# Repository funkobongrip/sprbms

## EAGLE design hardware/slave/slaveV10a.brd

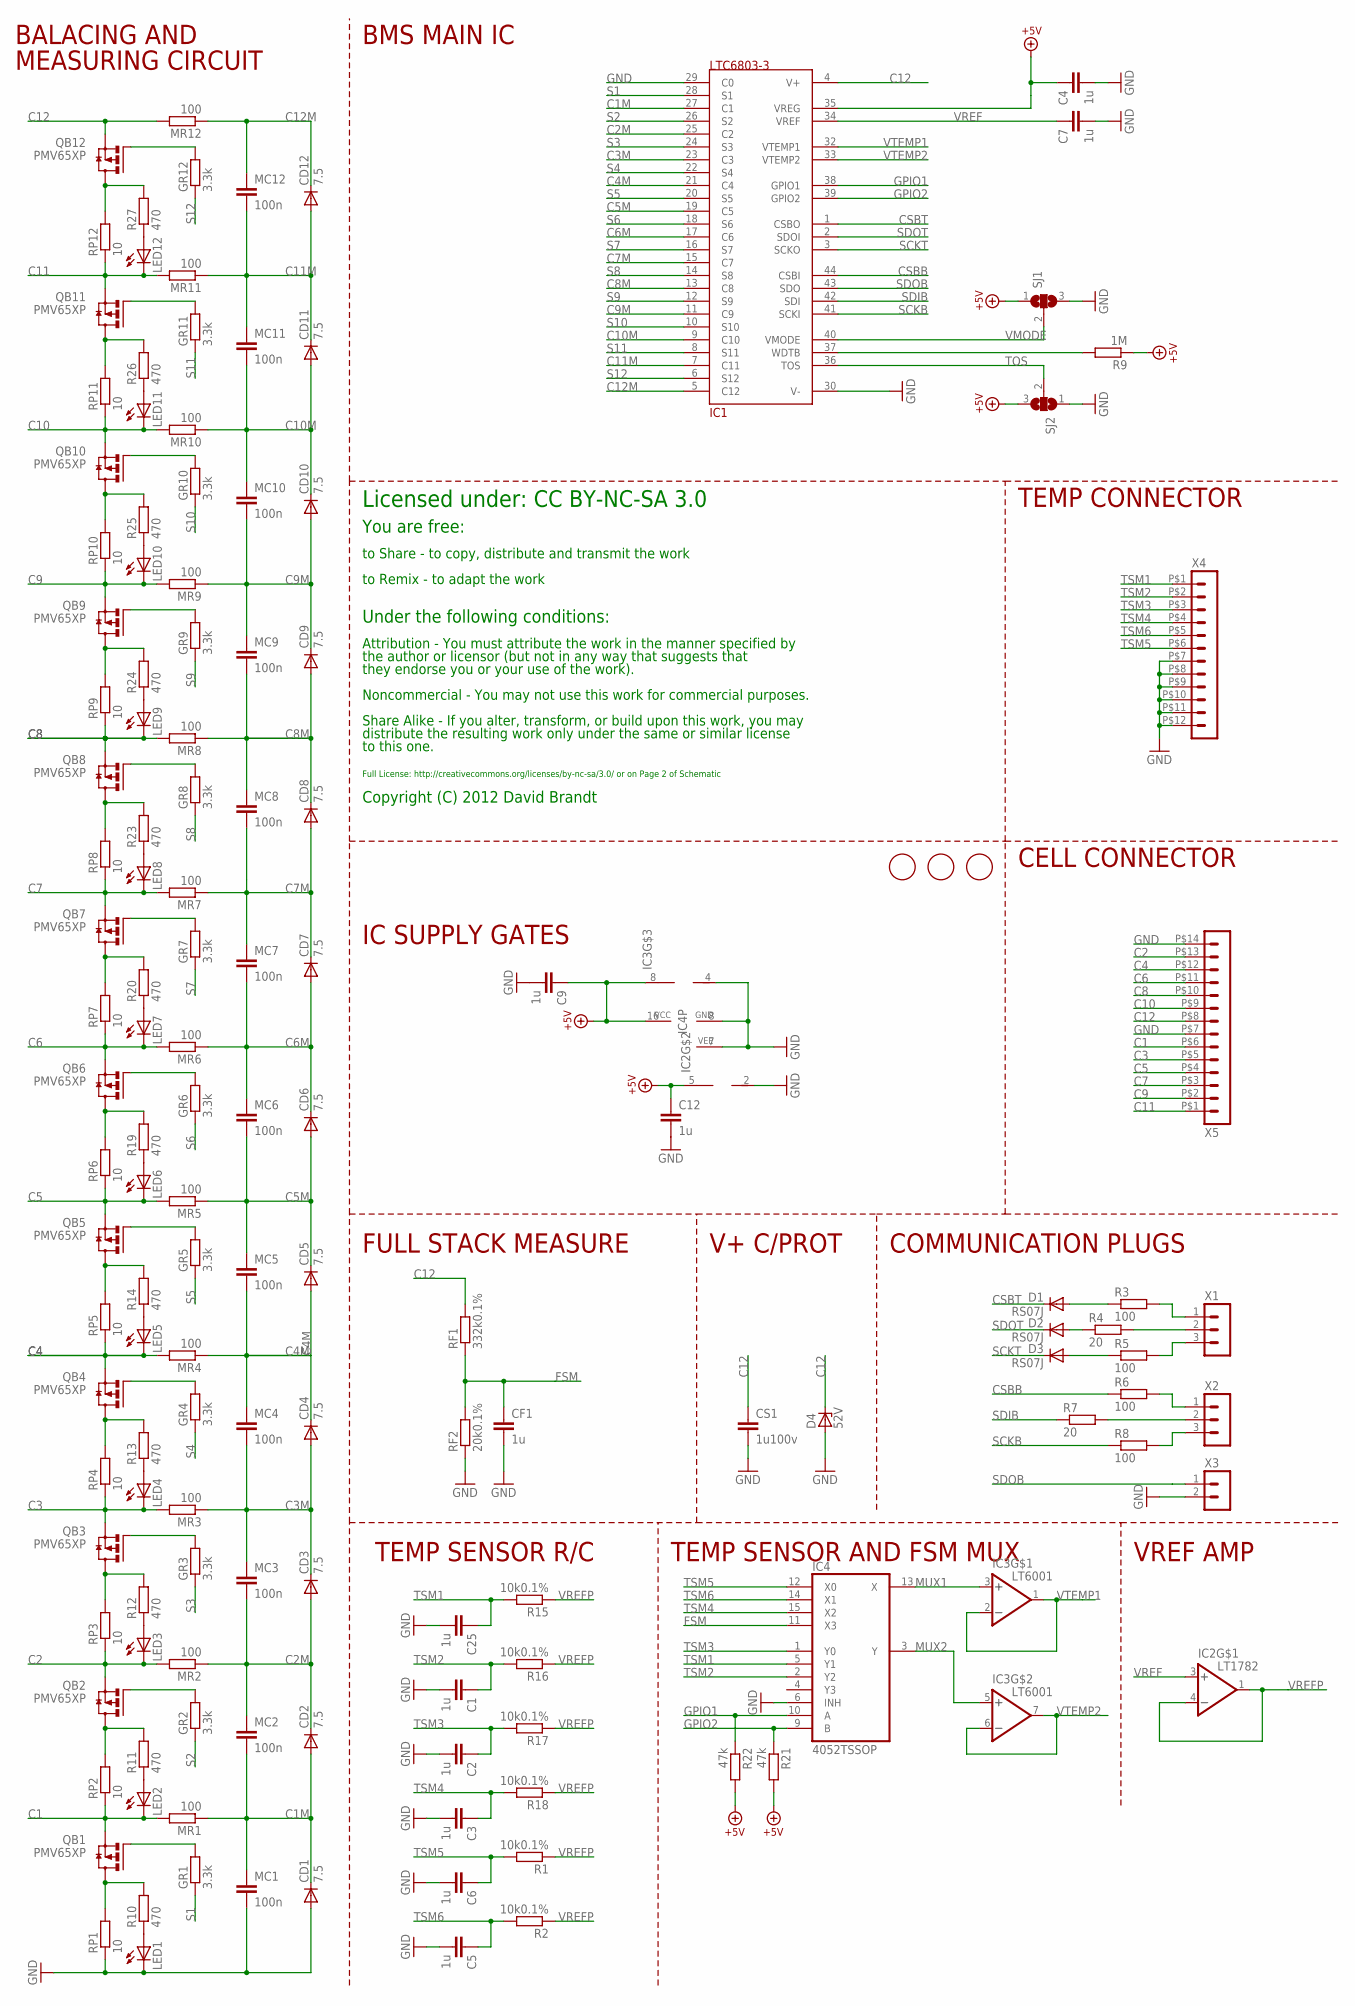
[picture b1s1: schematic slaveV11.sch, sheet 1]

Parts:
C1, C2, C3, C4, C5, C6, C7, C9, C12, C25: 1u; C0603
CD1, CD2, CD3, CD4, CD5, CD6, CD7, CD8, CD9, CD10, CD11, CD12: 7.5; SOD323-W
CF1: 1u; C0603
CS1: 1u100v; C1206K
D1, D2, D3: RS07J; DO-219AB
D4: 52V; SOD123
GR1, GR2, GR3, GR4, GR5, GR6, GR7, GR8, GR9, GR10, GR11, GR12: 3.3k; R0603
IC1: LTC6803-3; 44SSOP
IC2: LT1782; SOT23-5
IC3: LT6001; MS8
IC4: 4052TSSOP; TSSOP16
LED1, LED2, LED3, LED4, LED5, LED6, LED7, LED8, LED9, LED10, LED11, LED12: LEDCHIPLED_0805; CHIPLED_0805
MC1, MC2, MC3, MC4, MC5, MC6, MC7, MC8, MC9, MC10, MC11, MC12: 100n; C1206
MR1, MR2, MR3, MR4, MR5, MR6, MR7, MR8, MR9, MR10, MR11, MR12: 100; R0603
QB1, QB2, QB3, QB4, QB5, QB6, QB7, QB8, QB9, QB10, QB11, QB12: PMV65XP; SUPER-SOT3
R1, R2, R15, R16, R17, R18: 10k0.1%; R0603
R3, R5, R6, R8: 100; R0805
R4, R7: 20; R0805
R9: 1M; R0603
R10, R11, R12, R13, R14, R19, R20, R23, R24, R25, R26, R27: 470; R0603
R21, R22: 47k; R0603
REF1, REF2, REF3: FIDUCIALMOUNT; FIDUCIA-MOUNT
RF1: 332k0.1%; R0603
RF2: 20k0.1%; R0603
RP1, RP2, RP3, RP4, RP5, RP6, RP7, RP8, RP9, RP10, RP11, RP12: 10; SM_3
SJ1, SJ2: SJ2W; SJ_2
X1, X2: HEADER_POS3_43650-0315; 43650-0315
X3: HEADER_POS2_43650-0215; 43650-0215
X4: HEADER_POS12_43045-1212; 43045-1212
X5: HEADER_POS14_43045-1412; 43045-1412

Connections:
+5V: C4.1, C9.1, C12.1, IC1.35 (VREG), IC2.5 (V+), IC3.8 (V+), IC4.16 (VCC), R9.1, R21.2, R22.2, SJ1.1, SJ2.3
B1: QB1.3 (D), R10.2, RP1.P$2 (2)
B2: QB2.3 (D), R11.2, RP2.P$2 (2)
B3: QB3.3 (D), R12.2, RP3.P$2 (2)
B4: QB4.3 (D), R13.2, RP4.P$2 (2)
B5: QB5.3 (D), R14.2, RP5.P$2 (2)
B6: QB6.3 (D), R19.2, RP6.P$2 (2)
B7: QB7.3 (D), R20.2, RP7.P$2 (2)
B8: QB8.3 (D), R23.2, RP8.P$2 (2)
B9: QB9.3 (D), R24.2, RP9.P$2 (2)
B10: QB10.3 (D), R25.2, RP10.P$2 (2)
B11: QB11.3 (D), R26.2, RP11.P$2 (2)
B12: QB12.3 (D), R27.2, RP12.P$2 (2)
C1: LED2.C, MR1.2, QB1.2 (S), RP2.P$1 (1), X5.P$6 (6)
C1M: CD1.C, CD2.A, IC1.27 (C1), MC1.1, MC2.2, MR1.1
C2: LED3.C, MR2.2, QB2.2 (S), RP3.P$1 (1), X5.P$13 (13)
C2M: CD2.C, CD3.A, IC1.25 (C2), MC2.1, MC3.2, MR2.1
C3: LED4.C, MR3.2, QB3.2 (S), RP4.P$1 (1), X5.P$5 (5)
C3M: CD3.C, CD4.A, IC1.23 (C3), MC3.1, MC4.2, MR3.1
C4: LED5.C, MR4.2, QB4.2 (S), RP5.P$1 (1), X5.P$12 (12)
C4M: CD4.C, CD5.A, IC1.21 (C4), MC4.1, MC5.2, MR4.1
C5: LED6.C, MR5.2, QB5.2 (S), RP6.P$1 (1), X5.P$4 (4)
C5M: CD5.C, CD6.A, IC1.19 (C5), MC5.1, MC6.2, MR5.1
C6: LED7.C, MR6.2, QB6.2 (S), RP7.P$1 (1), X5.P$11 (11)
C6M: CD6.C, CD7.A, IC1.17 (C6), MC6.1, MC7.2, MR6.1
C7: LED8.C, MR7.2, QB7.2 (S), RP8.P$1 (1), X5.P$3 (3)
C7M: CD7.C, CD8.A, IC1.15 (C7), MC7.1, MC8.2, MR7.1
C8: LED9.C, MR8.2, QB8.2 (S), RP9.P$1 (1), X5.P$10 (10)
C8M: CD8.C, CD9.A, IC1.13 (C8), MC8.1, MC9.2, MR8.1
C9: LED10.C, MR9.2, QB9.2 (S), RP10.P$1 (1), X5.P$2 (2)
C9M: CD9.C, CD10.A, IC1.11 (C9), MC9.1, MC10.2, MR9.1
C10: LED11.C, MR10.2, QB10.2 (S), RP11.P$1 (1), X5.P$9 (9)
C10M: CD10.C, CD11.A, IC1.9 (C10), MC10.1, MC11.2, MR10.1
C11: LED12.C, MR11.2, QB11.2 (S), RP12.P$1 (1), X5.P$1 (1)
C11M: CD11.C, CD12.A, IC1.7 (C11), MC11.1, MC12.2, MR11.1
C12: CS1.1, D4.C, IC1.4 (V+), MR12.2, QB12.2 (S), RF1.2, X5.P$8 (8)
C12M: CD12.C, IC1.5 (C12), MC12.1, MR12.1
CSBB: IC1.44 (CSBI), R6.1
CSBBP: R6.2, X2.1
CSBT: D1.C, IC1.1 (CSBO)
CSBTK: D1.A, R3.1
CSBTP: R3.2, X1.1
FSM: CF1.1, IC4.11 (X3), RF1.1, RF2.2
GND: C1.2, C2.2, C3.2, C4.2, C5.2, C6.2, C7.2, C9.2, C12.2, C25.2, CD1.A, CF1.2, CS1.2, D4.A, IC1.29 (C0), IC1.30 (V-), IC2.2 (V-), IC3.4 (V-), IC4.6 (INH), IC4.7 (VEE), IC4.8 (GND), LED1.C, MC1.2, RF2.1, RP1.P$1 (1), SJ1.3, SJ2.1, X3.2, X4.P$7 (7), X4.P$8 (8), X4.P$9 (9), X4.P$10 (10), X4.P$11 (11), X4.P$12 (12), X5.P$7 (7), X5.P$14 (14)
GPIO1: IC1.38 (GPIO1), IC4.10 (A), R22.1
GPIO2: IC1.39 (GPIO2), IC4.9 (B), R21.1
L1C: LED1.A, R10.1
L2C: LED2.A, R11.1
L3C: LED3.A, R12.1
L4C: LED4.A, R13.1
L5C: LED5.A, R14.1
L6C: LED6.A, R19.1
L7C: LED7.A, R20.1
L8C: LED8.A, R23.1
L9C: LED9.A, R24.1
L10C: LED10.A, R25.1
L11C: LED11.A, R26.1
L12C: LED12.A, R27.1
MUX1: IC3.3 (+IN), IC4.13 (X)
MUX2: IC3.5 (+IN), IC4.3 (Y)
S1: GR1.1, IC1.28 (S1)
S1G: GR1.2, QB1.1 (G)
S1G1: GR2.2, QB2.1 (G)
S1G2: GR3.2, QB3.1 (G)
S1G3: GR4.2, QB4.1 (G)
S1G4: GR5.2, QB5.1 (G)
S1G5: GR6.2, QB6.1 (G)
S1G6: GR7.2, QB7.1 (G)
S1G7: GR8.2, QB8.1 (G)
S1G8: GR9.2, QB9.1 (G)
S1G9: GR10.2, QB10.1 (G)
S1G10: GR11.2, QB11.1 (G)
S1G11: GR12.2, QB12.1 (G)
S2: GR2.1, IC1.26 (S2)
S3: GR3.1, IC1.24 (S3)
S4: GR4.1, IC1.22 (S4)
S5: GR5.1, IC1.20 (S5)
S6: GR6.1, IC1.18 (S6)
S7: GR7.1, IC1.16 (S7)
S8: GR8.1, IC1.14 (S8)
S9: GR9.1, IC1.12 (S9)
S10: GR10.1, IC1.10 (S10)
S11: GR11.1, IC1.8 (S11)
S12: GR12.1, IC1.6 (S12)
SCKB: IC1.41 (SCKI), R8.1
SCKBP: R8.2, X2.3
SCKT: D3.C, IC1.3 (SCKO)
SCKTK: D3.A, R5.1
SCKTP: R5.2, X1.3
SDIB: IC1.42 (SDI), R7.1
SDIBP: R7.2, X2.2
SDOB: IC1.43 (SDO), X3.1
SDOT: D2.C, IC1.2 (SDOI)
SDOTK: D2.A, R4.1
SDOTP: R4.2, X1.2
TOS: IC1.36 (TOS), SJ2.2
TSM1: C25.1, IC4.5 (Y1), R15.2, X4.P$1 (1)
TSM2: C1.1, IC4.2 (Y2), R16.2, X4.P$2 (2)
TSM3: C2.1, IC4.1 (Y0), R17.2, X4.P$3 (3)
TSM4: C3.1, IC4.15 (X2), R18.2, X4.P$4 (4)
TSM5: C6.1, IC4.12 (X0), R1.2, X4.P$6 (6)
TSM6: C5.1, IC4.14 (X1), R2.2, X4.P$5 (5)
VMODE: IC1.40 (VMODE), SJ1.2
VREF: C7.1, IC1.34 (VREF), IC2.3 (+IN)
VREFP: IC2.1 (OUT), IC2.4 (-IN), R1.1, R2.1, R15.1, R16.1, R17.1, R18.1
VTEMP1: IC1.32 (VTEMP1), IC3.1 (OUT), IC3.2 (-IN)
VTEMP2: IC1.33 (VTEMP2), IC3.6 (-IN), IC3.7 (OUT)
WDTB: IC1.37 (WDTB), R9.2

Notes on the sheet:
TEMP CONNECTOR
CELL CONNECTOR
IC SUPPLY GATES
BALACING AND
BMS MAIN IC
TEMP SENSOR AND FSM MUX
MEASURING CIRCUIT
TEMP SENSOR R/C
VREF AMP
FULL STACK MEASURE
V+ C/PROT
COMMUNICATION PLUGS
Licensed under: CC BY-NC-SA 3.0
You are free:
to Share - to copy, distribute and transmit the work
to Remix - to adapt the work
Under the following conditions:
the author or licensor (but not in any way that suggests that
Attribution - You must attribute the work in the manner specified by
they endorse you or your use of the work).
Noncommercial - You may not use this work for commercial purposes.
Share Alike - If you alter, transform, or build upon this work, you may
distribute the resulting work only under the same or similar license
to this one.
Full License: http://creativecommons.org/licenses/by-nc-sa/3.0/ or on Page 2 of Schematic
Copyright (C) 2012 David Brandt

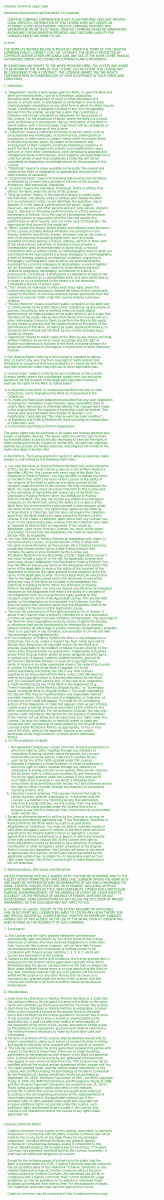
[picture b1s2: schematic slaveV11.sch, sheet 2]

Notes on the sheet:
Creative Commons Legal Code
Attribution-NonCommercial-ShareAlike 3.0 Unported
CREATIVE COMMONS CORPORATION IS NOT A LAW FIRM AND DOES NOT PROVIDE
LEGAL SERVICES. DISTRIBUTION OF THIS LICENSE DOES NOT CREATE AN
ATTORNEY-CLIENT RELATIONSHIP. CREATIVE COMMONS PROVIDES THIS
INFORMATION ON AN "AS-IS" BASIS. CREATIVE COMMONS MAKES NO WARRANTIES
REGARDING THE INFORMATION PROVIDED, AND DISCLAIMS LIABILITY FOR
DAMAGES RESULTING FROM ITS USE.
License
THE WORK (AS DEFINED BELOW) IS PROVIDED UNDER THE TERMS OF THIS CREATIVE
COMMONS PUBLIC LICENSE ("CCPL" OR "LICENSE"). THE WORK IS PROTECTED BY
COPYRIGHT AND/OR OTHER APPLICABLE LAW. ANY USE OF THE WORK OTHER THAN AS
AUTHORIZED UNDER THIS LICENSE OR COPYRIGHT LAW IS PROHIBITED.
BY EXERCISING ANY RIGHTS TO THE WORK PROVIDED HERE, YOU ACCEPT AND AGREE
TO BE BOUND BY THE TERMS OF THIS LICENSE. TO THE EXTENT THIS LICENSE MAY
BE CONSIDERED TO BE A CONTRACT, THE LICENSOR GRANTS YOU THE RIGHTS
CONTAINED HERE IN CONSIDERATION OF YOUR ACCEPTANCE OF SUCH TERMS AND
CONDITIONS.
1. Definitions
a. "Adaptation" means a work based upon the Work, or upon the Work and
other pre-existing works, such as a translation, adaptation,
derivative work, arrangement of music or other alterations of a
literary or artistic work, or phonogram or performance and includes
cinematographic adaptations or any other form in which the Work may be
recast, transformed, or adapted including in any form recognizably
derived from the original, except that a work that constitutes a
Collection will not be considered an Adaptation for the purpose of
this License. For the avoidance of doubt, where the Work is a musical
work, performance or phonogram, the synchronization of the Work in
timed-relation with a moving image ("synching") will be considered an
Adaptation for the purpose of this License.
b. "Collection" means a collection of literary or artistic works, such as
encyclopedias and anthologies, or performances, phonograms or
broadcasts, or other works or subject matter other than works listed
in Section 1(g) below, which, by reason of the selection and
arrangement of their contents, constitute intellectual creations, in
which the Work is included in its entirety in unmodified form along
with one or more other contributions, each constituting separate and
independent works in themselves, which together are assembled into a
collective whole. A work that constitutes a Collection will not be

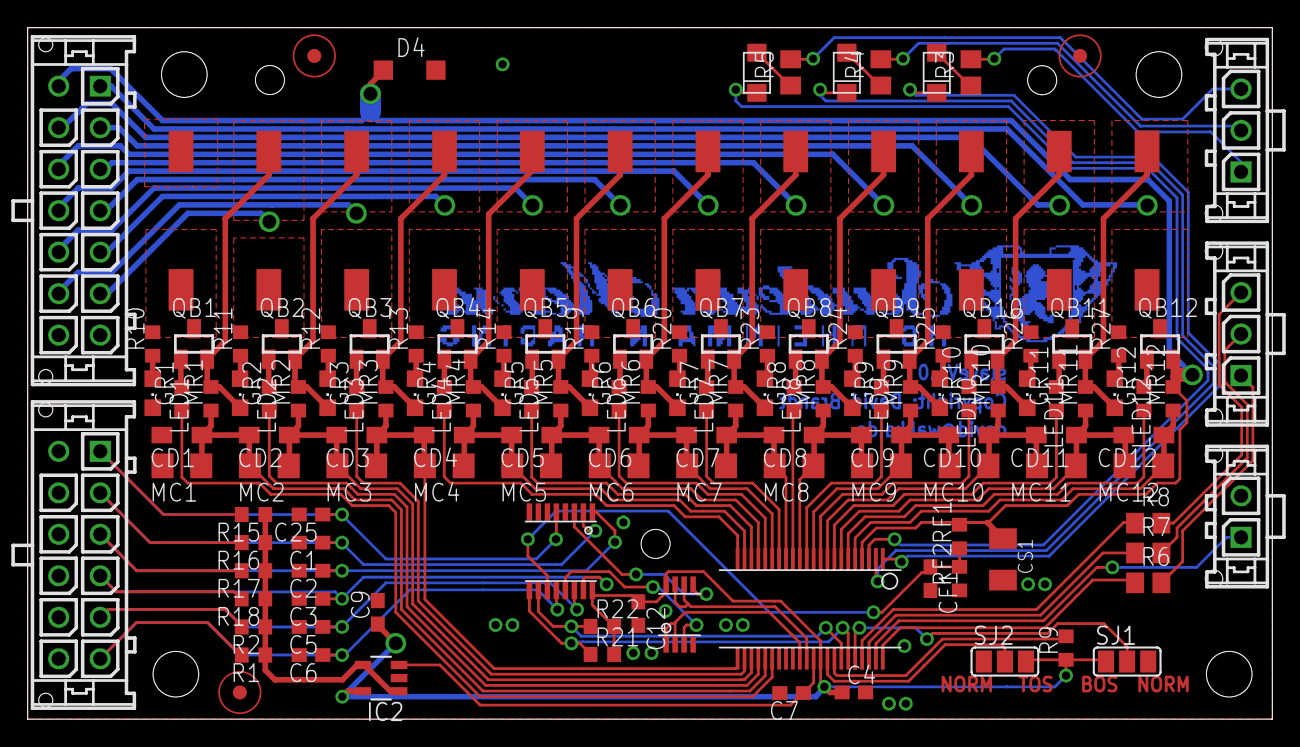
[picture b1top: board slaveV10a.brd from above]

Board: 2 copper layers, 90.0 x 50.0 mm, 144 parts (1 on the bottom side), 108 nets.

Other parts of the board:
U$7: SMLOGO

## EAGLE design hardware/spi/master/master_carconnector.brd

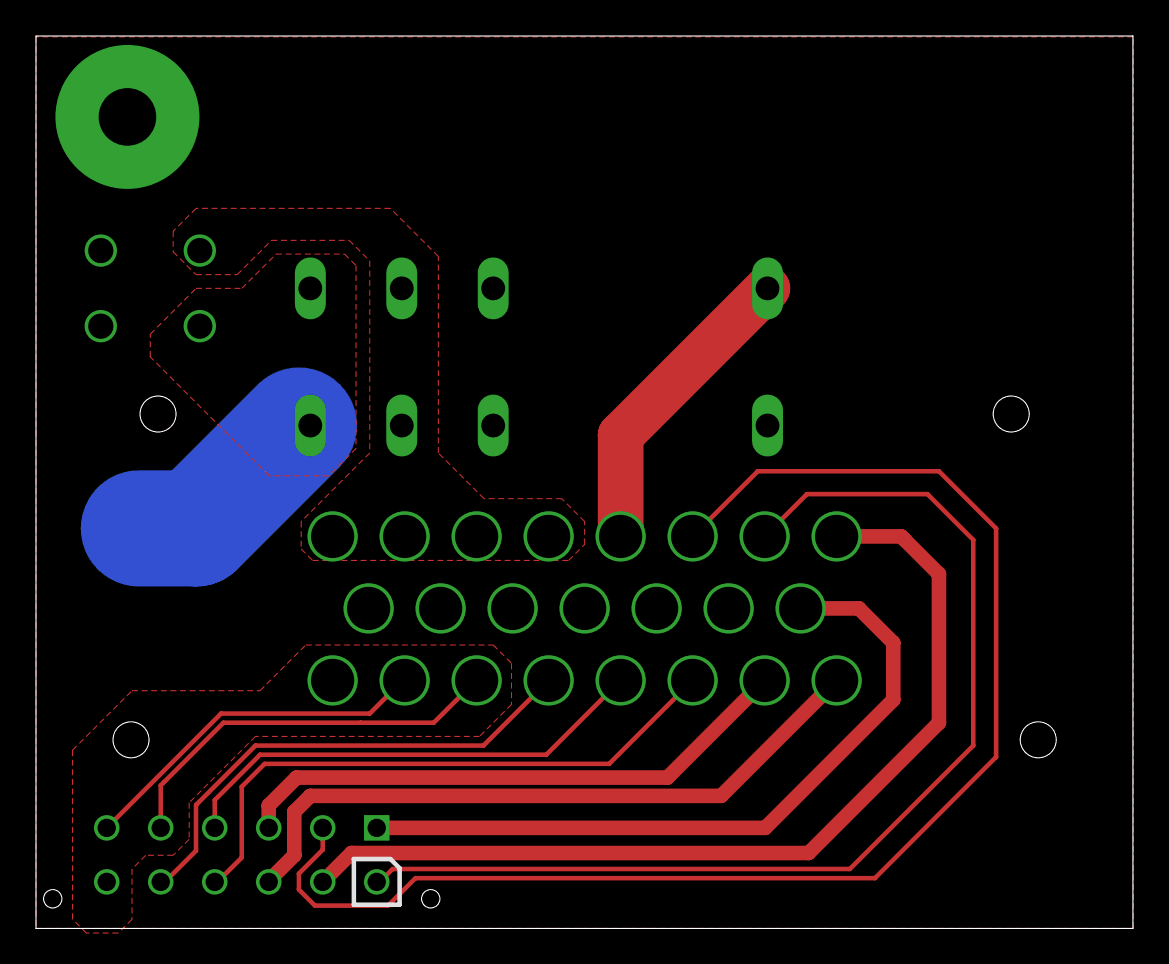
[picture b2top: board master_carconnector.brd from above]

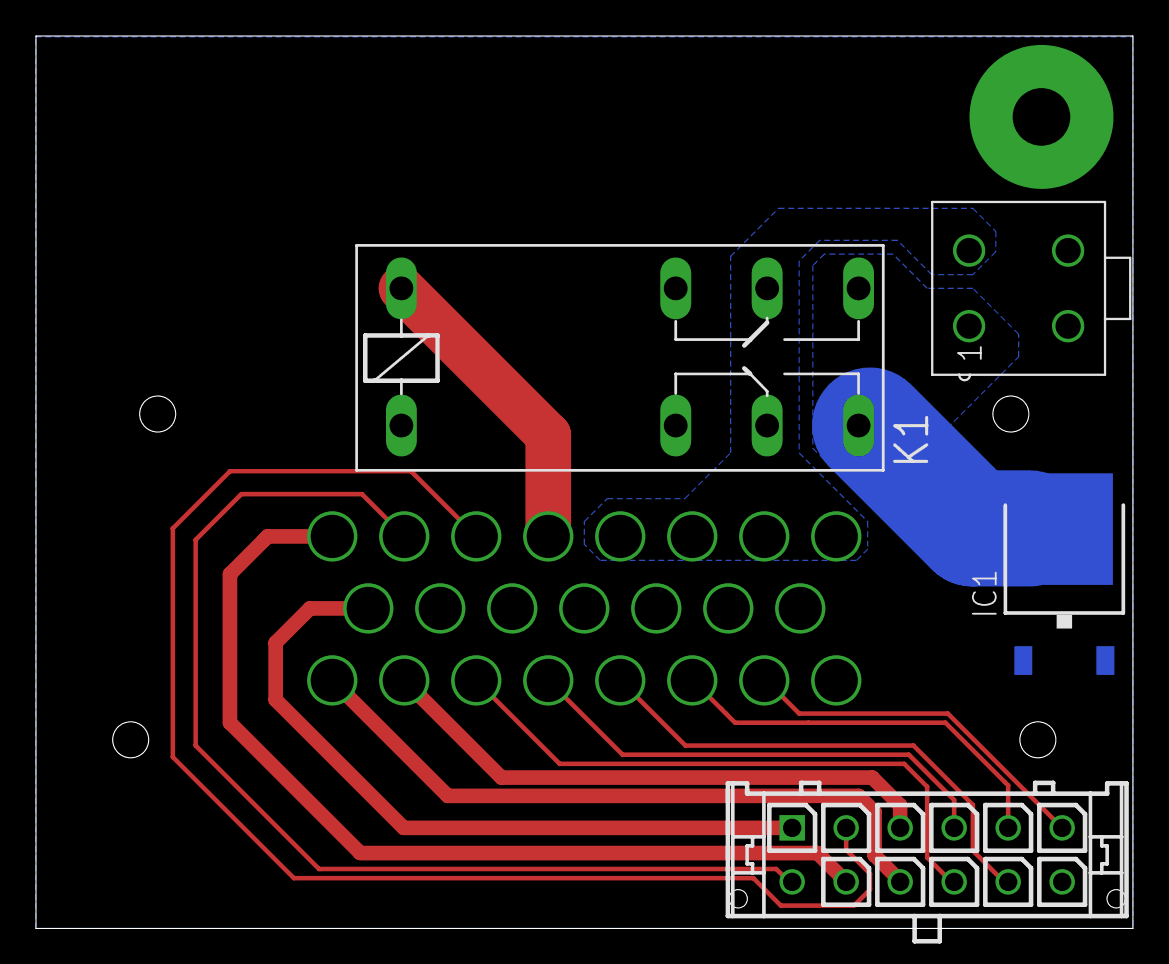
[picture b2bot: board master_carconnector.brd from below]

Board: 2 copper layers, 60.9 x 49.6 mm, 5 parts (4 on the bottom side), 16 nets.

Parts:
IC1: DIODE: 2075028; TO252
K1: 4052; F4052
X2: MINI-FIT-JR-045566; 5566-04
X3: AMPSEAL23STR; AMPSEAL23-STR
X10: 43045-1212

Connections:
CANGND: X3.P$16, X10.P$12
CANH: X3.P$17, X10.P$6
CANL: X3.P$18, X10.P$5
CAR+12V: K1.P1, K1.P2, X2.P2, X3.P$1, X3.P$2, X3.P$3, X3.P$4
CARGND: IC1.2, K1.2, X2.P3, X2.P4, X3.P$9, X3.P$10, X3.P$11, X3.P$12, X3.P$13, X3.P$14
DCDCRELAI: X3.P$8, X10.P$8
DISCHARGE+: X3.P$22, X10.P$3
DISCHARGE-: X3.P$23, X10.P$9
EMERGENCYIN: X3.P$7, X10.P$7
EMERGENCYOUT: X3.P$6, X10.P$2
GPIO: X3.P$21, X10.P$10
RELAI+12V: IC1.3, K1.S1, K1.S2, X2.P1
RELAI+12VC: K1.1, X3.P$5
RX: X3.P$20, X10.P$4
TSAL: X3.P$15, X10.P$1
TX: X3.P$19, X10.P$11

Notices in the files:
hardware/slave/slaveV10a.brd:
Copyright: David Brandt
hardware/slave/slaveV11.sch:
as selected by Licensor and indicated in the title of this License:
offer(s) the Work under the terms of this License.
Licensor to exercise rights under this License despite a previous
recipient under the terms of the License. You may not sublicense the
the same License Elements as this License; (iii) a Creative Commons
recipient under the terms of the Applicable License. This Section 4(b)
exercise by You of the rights granted under this License;
You of the rights granted under this License if Your exercise of
